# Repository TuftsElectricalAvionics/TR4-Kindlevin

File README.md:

The code repository for everything related to to the TR4 Kindlevin rocket including code for the flight computer, airbrakes and the rocket tracking antenna.

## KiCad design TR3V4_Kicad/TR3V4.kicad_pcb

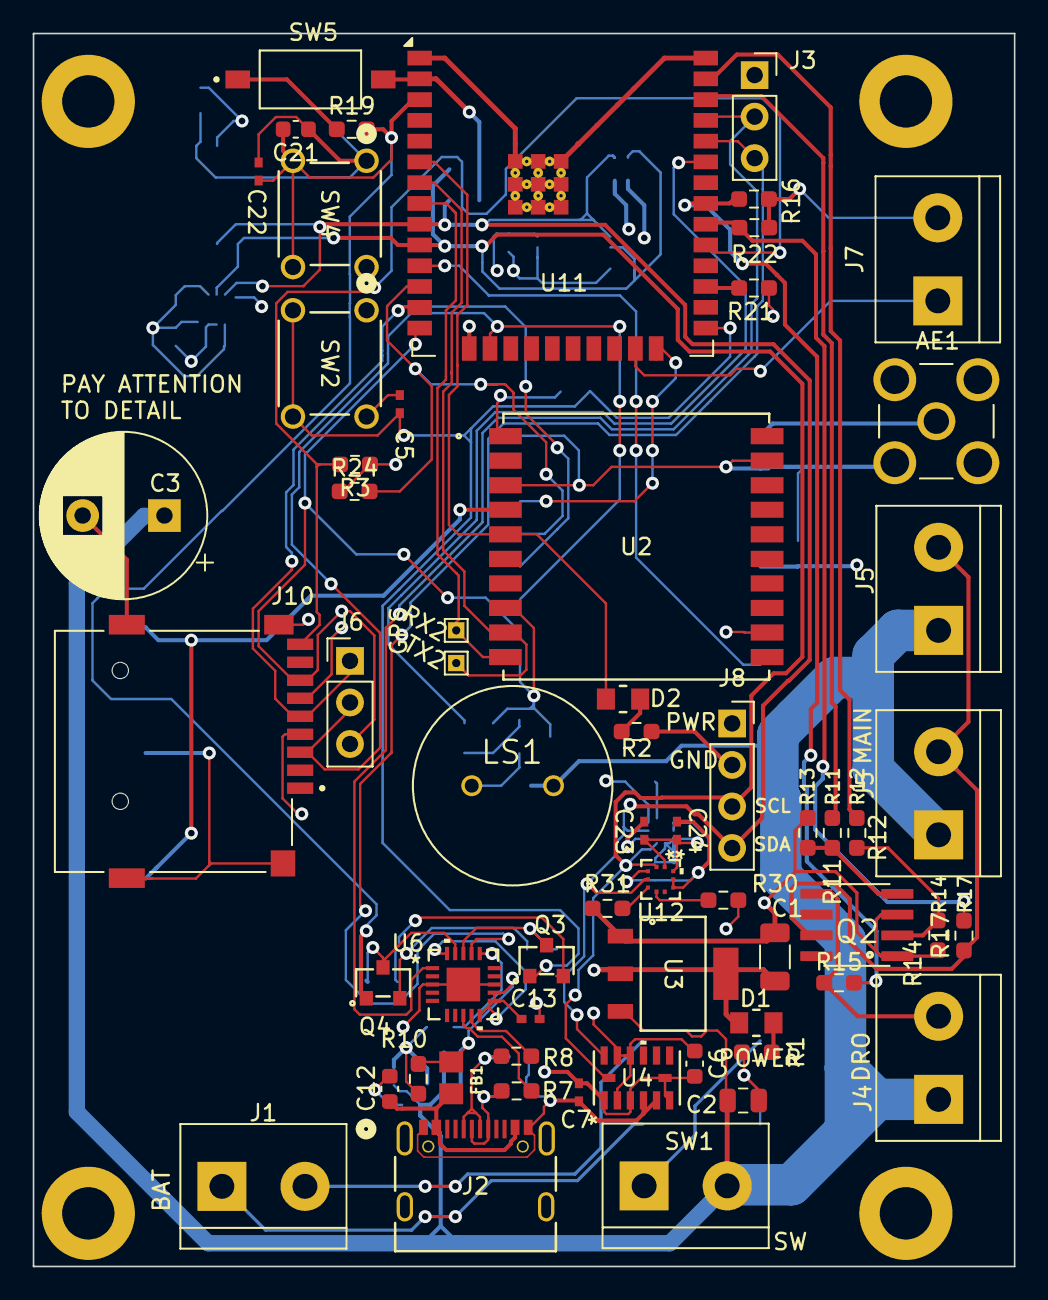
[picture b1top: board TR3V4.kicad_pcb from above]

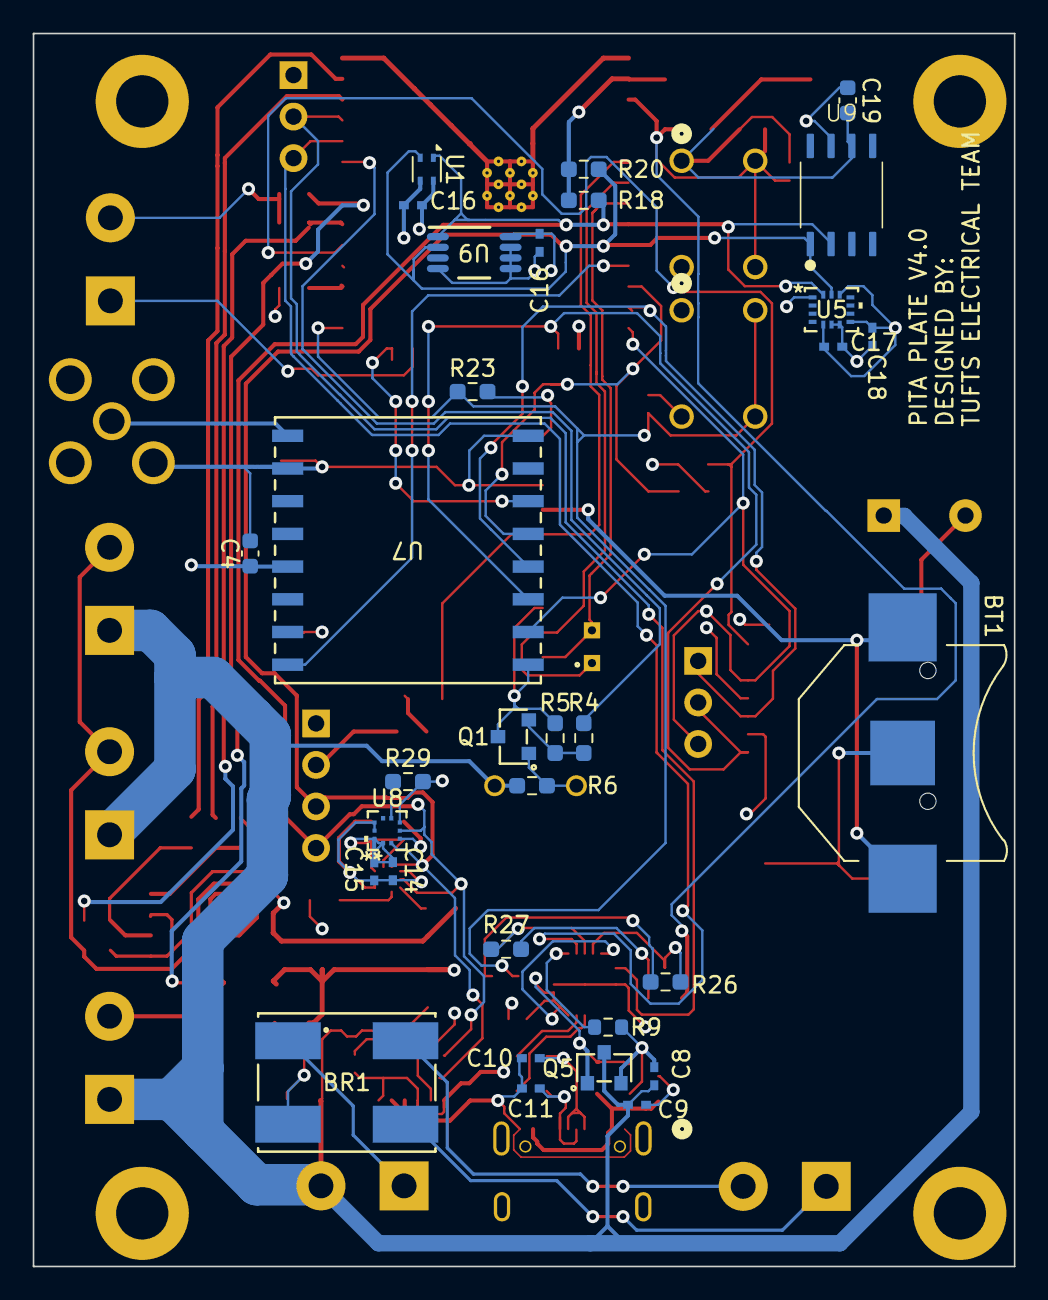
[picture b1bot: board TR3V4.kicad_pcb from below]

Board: 4 copper layers, 60.0 x 75.4 mm, 93 parts (32 on the bottom side), 55 nets.

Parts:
AE1: Antenna; GRADCONN_RFPC-SMA28-F
BR1: Z4DGP406L-HF; Z4DGP406L-HF_footprint_N
BT1: 3.0 Coin Cell; BAT_BK-885
C1: 100 uF; C_1206_3216Metric
C2: 10 uF; C_0805_2012Metric
C3: 2200 uF; CP_Radial_D10.0mm_P5.00mm
C4, C6, C19, C21: 1 uF; C_0603_1608Metric
C5, C7, C8, C9, C14, C15, C16, C16#2, C17, C18, C22, C23, C24: 0.1 uF; CAP_CL05_SAM
C10, C11: 47pf; G-155_MUR
C12: 10 nf; C_0603_1608Metric
C13: 100 nf; CAP_CL05_SAM
D1, D2: LED; 150080RS75000_WRE
FB1: FerriteBead; FB_MI0805K400R-10
J1, J4, J5, J5#2, J7: Screw_Terminal_01x02; TerminalBlock_bornier-2_P5.08mm
J2: USB4105-GF-A; USB4105_GCT
J3: Conn_01x03_Pin; PinSocket_1x03_P2.54mm_Vertical
J6: Conn_01x03_Pin; PinHeader_1x03_P2.54mm_Vertical
J8: Conn_01x04_Pin; PinSocket_1x04_P2.54mm_Vertical
J10: MSD-4-A; CUI_MSD-4-A
LS1: PS1240P02BT; XDCR_PS1240P02BT
Q1, Q3, Q4, Q5: NPN; SMT_BJT_SP2
Q2: AO4838; MOSFET_Smt_2_sp2
R1: 1500 Ohm; R_0603_1608Metric_Pad0.98x0.95mm_HandSolder
R2: 1.5K Ohm; R_0603_1608Metric_Pad0.98x0.95mm_HandSolder
R3, R18, R20, R23, R24: 4.7k; R_0603_1608Metric_Pad0.98x0.95mm_HandSolder
R4, R11, R12: 100; R_0603_1608Metric_Pad0.98x0.95mm_HandSolder
R5, R10, R13, R14, R19, R21, R26, R27, R29, R30: 10k; R_0603_1608Metric_Pad0.98x0.95mm_HandSolder
R6: 1.5k; R_0603_1608Metric_Pad0.98x0.95mm_HandSolder
R7, R8: 27R; R_0603_1608Metric_Pad0.98x0.95mm_HandSolder
R9: 1k; R_0603_1608Metric
R15, R17: 130k; R_0603_1608Metric_Pad0.98x0.95mm_HandSolder
R16, R22, R31: 100k; R_0603_1608Metric_Pad0.98x0.95mm_HandSolder
RX2: TestPoint_Small; TestPoint_THTPad_1.0x1.0mm_Drill0.5mm
SW1: SW_SPST; TerminalBlock_bornier-2_P5.08mm
SW2, SW4: reset; SW_TS02-66-50-BK-XXX-LCR-D_CUD
SW5: Enable Switch; SW_DS04-254-2-01BK-SMT
TX2: TestPoint_Small; TestPoint_THTPad_1.0x1.0mm_Drill0.5mm
U1: Env. Temp; Sensirion_DFN-4_1.5x1.5mm_P0.8mm_SHT4x_NoCentralPad
U2: GPS; 5186_footprint_N
U3: LDL1117S33R; SOT223_STM
U4: High g Acceleromter; ADXL375BCCZ_footprint_N
U5: IMU; BMI323_BOS
U6: FT231XQ-R; FT231XQ-R_footprint_N
U7: COM-13909; COM-13909_footprint_N
U8: Barometer 1; QFN10_BMP581_BOS
U9: TMP1075DGKR; TMP1075DGKR_footprint_N
U9#2: Magnetometer; MAGNETO-MLX90395KDC
U11: ESP32-WROOM-32E-N8; ESP32-WROOM-32E
U12: Barometer 2; QFN10_BMP581_BOS

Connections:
+3.3V: C1.2, C4.2, C6.2, C7.2, C14.2, C15.1, C16.1, C16#2.2, C17.1, C18.1, C19.1, C23.2, C24.1, D1.2 (A), J8.1, J10.4 (VDD), R3.1, R18.1, R20.1, R21.2, R23.2, R24.1, R29.2, R30.2, SW5.2, U1.3 (VDD), U2.1 (VCC), U3.2 (VOUT), U3.4 (VOUT), U4.1 (VDD_I/O), U4.3 (RESERVED), U4.6 (VS), U4.7 (*CS), U5.5 (VDDIO), U5.8 (VDD), U5.12 (CSB), U7.13 (3.3V), U8.1 (VDDIO), U8.5 (SDO), U8.10 (VDD), U9.8 (V+), U9#2.7 (Vdd), U11.2 (3V3), U12.1 (VDDIO), U12.10 (VDD)
+7.5V: C2.2, C3.1, C8.1, C9.1, J4.1, J5.1, J5#2.1, LS1.2, Q5.3 (E), R6.1, SW1.2 (B), U3.3 (VIN)
/DN: C10.1, J2.A7 (DN1), J2.B7 (DN2), R8.1
/DP: C11.1, J2.A6 (DP1), J2.B6 (DP2), R7.1
/Detect: R9.2, U6.16 (CBUS3)
/Drouge: R11.1, U11.36 (IO22)
/I2C_SCL: J8.3, R20.2, U1.2 (SCL), U4.14 (SCL/SCLK), U5.13 (SCX), U8.2 (SCK), U9.2 (SCL), U9#2.1 (SCL), U11.10 (IO25), U12.2 (SCK)
/I2C_SDA: J8.4, R18.2, U1.1 (SDA), U4.13 (SDA/SDI/SDIO), U5.14 (SDX), U8.4 (SDI), U9.1 (SDA), U9#2.2 (SDA), U11.9 (IO33), U12.4 (SDI)
/LORA_CS: R24.2, U7.5 (NSS), U11.12 (IO27)
/LORA_Data02: U7.16 (DIO02), U11.11 (IO26)
/LORA_Reset: U7.6 (RESET), U11.24 (IO2)
/Main: R12.1, U11.37 (IO23)
/Motor_PWM: J7.1, U11.23 (IO15)
/SPICLK: J6.1, J10.5 (CLK), U7.4 (SCK), U11.13 (IO14)
/SPI_MISO: J6.3, J10.7 (DAT0), U7.2 (MISO), U11.14 (IO12)
/SPI_MOSI: J6.2, J10.3 (CMD), U7.3 (MOSI), U11.16 (IO13)
/UART_RX: J3.3, U6.17 (TXD), U11.34 (RXD0)
/UART_TX: J3.2, U6.1 (RXD), U11.35 (TXD0)
/VBUS: C12.1, FB1.1, J2.A4-B9 (VBUS), J2.B4-A9 (VBUS)
/VCC: C13.1, FB1.2, Q5.1 (C), R10.2, U6.10 (3V3OUT), U6.11 (RESET#), U6.12 (VCC), U6.20 (VCCIO)
/cont drouge: R15.2, R16.1, U11.31 (IO19)
/cont main: R17.2, R22.1, U11.30 (IO18)
/cs_sd: J10.CD, R3.2, U11.29 (IO5)
/fix: D2.2 (A), U2.5 (3D-FIX), U11.6 (IO34)
/flash: C5.2, Q3.1 (C), R23.1, SW2.2, U11.25 (IO0)
/gps_rx: RX2.1, U2.10 (RX0), U11.8 (IO32)
/gps_tx: TX2.1, U2.9 (TX0), U11.7 (IO35)
/piezo: R4.2, U11.33 (IO21)
/reset: C21.2, C22.2, Q4.1 (C), R19.2, SW4.2, U11.3 (EN)
Earth: AE1.G1, AE1.G2, AE1.G3, AE1.G4, BR1.4, BT1.2 (-), C1.1, C2.1, C3.2, C4.1, C5.1, C6.1, C7.1, C9.2, C10.2, C11.2, C12.2, C13.2, C14.1, C15.2, C16.2, C16#2.1, C17.2, C18.2, C19.2, C21.1, C22.1, C23.1, C24.2, J2.A1-B12 (GND), J2.B1-A12 (GND), J3.1, J7.2, J8.2, J10.6 (VSS), J10.G1 (COVER_GND), J10.G2 (COVER_GND__1), J10.G3 (COVER_GND__2), J10.G4 (COVER_GND__3), Q1.3 (E), Q2.1, Q2.3, R1.2, R2.2, R5.1, R13.1, R14.1, R16.2, R22.2, R31.2, SW2.1, SW4.1, U1.4 (VSS), U2.3 (GND), U2.8 (GND), U2.12 (GND), U2.19 (GND), U3.1 (GND), U4.2 (GND), U4.4 (GND), U4.5 (GND), U4.11 (RESERVED), U4.12 (SDO/ALT_ADDRESS), U5.1 (SDO), U5.6 (GNDIO), U5.7 (GND), U6.3 (GND), U6.13 (GND), U6.21 (GND), U7.1 (GND), U7.8 (GND), U7.10 (GND), U8.3 (VSS), U8.8 (VSS), U8.9 (VSS), U9.4 (GND), U9.5 (A2), U9.6 (A1), U9.7 (A0), U9#2.6 (Vss), U11.1 (GND), U11.15 (GND), U11.38 (GND), U11.39 (GND), U12.3 (VSS), U12.8 (VSS), U12.9 (VSS)
unnamed: BT1.1 (+), U2.4 (VBACKUP)
unnamed: D1.1 (K), R1.1
unnamed: D2.1 (K), R2.1
unnamed: BR1.3, J1.1
unnamed: BR1.2, J1.2
unnamed: J4.2, Q2.5, R15.1
unnamed: J5.2, J5#2.2, Q2.7, R17.1
unnamed: Q1.2 (B), R4.1, R5.2
unnamed: LS1.1, Q1.1 (C), R6.2
unnamed: Q2.2, R12.2, R14.2
unnamed: Q2.4, R11.2, R13.2
unnamed: Q3.2 (B), R26.1
unnamed: Q3.3 (E), R27.2, U6.18 (DTR#)
unnamed: Q4.2 (B), R27.1
unnamed: Q4.3 (E), R26.2, U6.19 (RTS#)
unnamed: C8.2, Q5.2 (B), R9.1, R10.1
unnamed: R19.1, SW5.1
unnamed: BR1.1, SW1.1 (A)
unnamed: R8.2, U6.9 (USBDM)
unnamed: R7.2, U6.8 (USBDP)
unnamed: AE1.1, U7.9 (ANT)
unnamed: R29.1, U8.6 (CSB)
unnamed: R21.1, U11.27 (IO16)
unnamed: R30.1, U12.6 (CSB)
unnamed: R31.1, U12.5 (SDO)

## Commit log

2025-10-02 real first commit git push origin main --force git pushls test
2025-10-02 first operational board
2025-10-02 initial test commits
2025-10-02 added SD breakout to git
2025-10-02 fixed name
2025-10-02 added decimals to GPS readings for accuracy, removed extra column in data output, set clock
2025-10-12 create example esp project in ground station
2025-10-12 Actually esp-idf code is flight computer, not ground station
2025-10-12 Remove REPL code
2025-10-12 Remove REPL includes
2025-10-12 Remove command registration functions
2025-10-13 Full remove repl code
2025-10-13 Add temperature wrapper
2025-10-13 Rename files and fix temperature reading
2025-10-13 Add accelerometer
2025-10-13 Add IMU
2025-10-13 feat(flight-computer): add esp-idf port
2025-10-13 chore(flight-computer): update project name
2025-10-13 fix typo
2025-10-13 docs: document i2c abort condition
2025-10-13 chore: add formatter config
2025-10-14 Rename Figure_1.png to SampleData.png
2025-10-17 refactor: move error in TRY() macro
2025-10-17 feat(TMP1075): add config & connection checks
2025-10-19 Add clarifying comment
2025-10-19 WIP: add high-g accel (need to switch to new I2C functions)
2025-10-19 Use I2C write functions that will exist
2025-10-19 Add IMU accel/gyro
2025-10-19 refactor: resolve review comments
2025-10-19 refactor: remove copy constructor
2025-10-20 Add little endian read/write functions
2025-11-14 temp & magnetometer
2025-11-16 New KiCad version control
2025-11-16 Change Result to Expected and add config for BMI323
2025-11-16 First code for the BMI323
2025-11-16 Add new imu sensor and config code
2025-11-16 Add very basic 7-segment driver
2025-11-16 Explicitly delete copy constructors
2025-11-16 Add magnometer
2025-11-17 Rename 'Result' to 'Expected'
2025-11-21 add character maps for 7 segment
2025-11-23 Add segment display manager
2025-11-23 Add class for barometer sensors
2026-01-22 Add basic uart library
2026-01-22 Add proper constructors and destructors for uart
2026-02-01 Build successful
2026-02-01 Fix some compile errors
2026-02-08 Fix all remaining compiler errors
2026-02-08 Fix compiler errors for sd
2026-02-08 fix some warnings about missing initializers
2026-02-08 Add flight computer class
2026-02-08 initialize all sensors
2026-02-08 Only start 7segment timer if it isn't already running
2026-02-08 Create Logger task
2026-02-15 Add flush files
2026-02-15 Add basic imu writing code
2026-02-15 Finish rebasing into feat/flightcomp
2026-02-15 add helpful comments
2026-02-15 Add I2C manager
2026-02-21 WIP fix csv and imu settings
2026-02-22 WIP baro sensors
2026-02-22 WIP add high g accel reading
2026-02-22 make flight computer ready to fly
2026-02-22 make high g accel and barometer reads in series
2026-02-27 WIP improve write hertz
2026-02-28 WIP improve data latency
2026-03-01 revert to buffer style
2026-03-02 working good test of multicore execution, demonstrating one task being blocked while the other isn't
2026-03-02 Add warning about potential UB
2026-03-03 WIP print sensor data in different thread
2026-03-09 WIP write with both tasks to check corruption
2026-03-09 WIP, with delays no data corruption (just differences in line breaks)
2026-03-13 WIP drogue deployment
2026-03-13 Add main deployment code
2026-03-13 add backup code
2026-03-14 WIP srad rrc3
2026-03-15 known-good rtos writer (slow)
2026-03-15 known good rtos writer with double bu buffering
2026-03-15 mount and unmount twice
2026-03-15 no drops, no corrupts
2026-03-15 known good version (14k lines, no drops, 56 >0.5s gaps)
2026-03-15 remove initial double writing
2026-03-15 remove all double writing artifacts
2026-03-15 write raw files instead of csv
2026-03-15 optimize write size
